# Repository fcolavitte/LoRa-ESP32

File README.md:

# LoRa-ESP32
Proyecto de comunicación unidireccional de USB a LoRa para pruebas de comunicación con satelites LEO para la empresa Satellogic.
El dispositivo toma datos por Wi-Fi y USB y envía mensajes por módulo LoRa E22 a satélites LEO.

El proyecto cuenta con una interfaz de usuario por USB con un menu interactivo por medio de los números del teclado.
La interfaz USB también admite comandos específicos.

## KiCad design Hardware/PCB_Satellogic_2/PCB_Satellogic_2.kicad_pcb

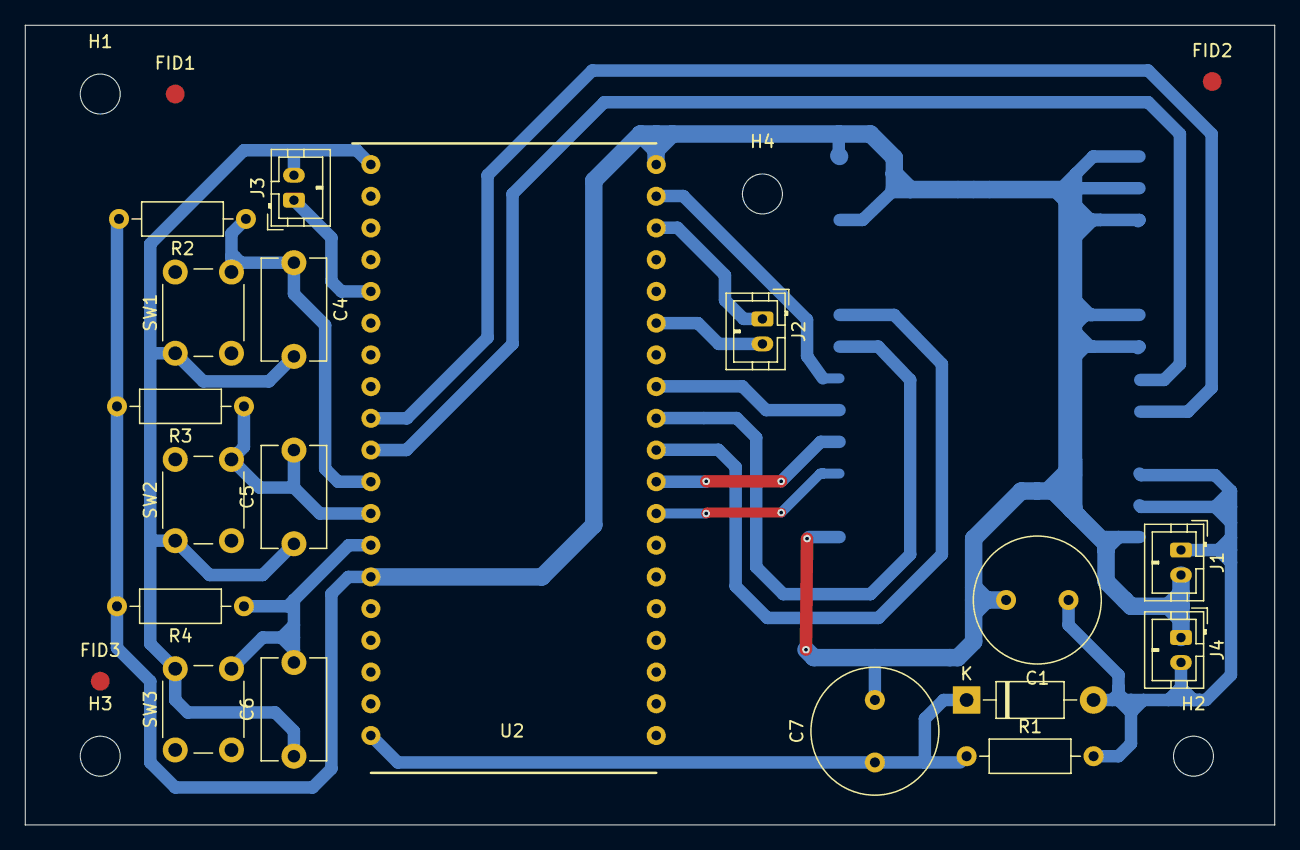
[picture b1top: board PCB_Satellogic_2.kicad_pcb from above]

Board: 2 copper layers, 100.0 x 64.0 mm, 26 parts (1 on the bottom side), 18 nets.

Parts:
C1: 470uF; C_Radial_D10.0mm_H16.0mm_P5.00mm
C4, C5, C6: 10nF; C_Disc_D8.0mm_W5.0mm_P7.50mm
C7: 4.7uF; C_Radial_D10.0mm_H16.0mm_P5.00mm
D1: 1N5819; D_DO-41_SOD81_P10.16mm_Horizontal
FID1, FID2, FID3: Fiducial; Fiducial_1.5mm_Mask3mm
H1, H2, H3, H4: MountingHole; MountingHole_3.2mm_M3
J1: 5V_out; JST_PH_B2B-PH-K_1x02_P2.00mm_Vertical
J2: I2C; JST_PH_B2B-PH-K_1x02_P2.00mm_Vertical
J3: ADC; JST_PH_B2B-PH-K_1x02_P2.00mm_Vertical
J4: 5V_in; JST_PH_B2B-PH-K_1x02_P2.00mm_Vertical
R1: 100R; R_Axial_DIN0207_L6.3mm_D2.5mm_P10.16mm_Horizontal
R2, R3, R4: 2k2; R_Axial_DIN0207_L6.3mm_D2.5mm_P10.16mm_Horizontal
SW1: SetRXMode; SW_PUSH_6mm_H4.3mm
SW2: TX; SW_PUSH_6mm_H4.3mm
SW3: SetWiFiMode; SW_PUSH_6mm_H4.3mm
U1: E22-900M30S_LoRa; E22-900M30S_LoRa_smd
U2: Node-MCU_ESP32_38PINES; Node-MCU_ESP32_38PINES_THT_offset

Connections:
/3v3: C4.2, C5.1, C6.1, J3.2, SW1.1, SW2.1, SW3.1, U2.1 (3.3V)
/5V: C1.1, D1.2 (A), J1.1, J4.2, R1.2, U1.9 (Vcc), U1.10 (Vcc)
/ADC: J3.1, U2.5 (GPIO34)
/BUSY: U1.14 (BUSY), U2.27 (Rx2-GPIO16)
/MISO: U1.16 (MISO), U2.31 (MISO-GPIO19)
/MOSI: U1.17 (MOSI), U2.37 (MOSI-GPIO23)
/NSS: U1.19 (NSS), U2.29 (CS0-GPIO5)
/RST_E22: U1.15 (NRST), U2.28 (Tx2-GPIO17)
/RXEN: U1.6 (RXEN), U2.10 (GPIO26)
/SCK: U1.18 (SCK), U2.30 (CLK-GPIO18)
/SCL: J2.1, U2.36 (GPIO22)
/SDA: J2.2, U2.33 (GPIO21)
/SetRxMode: C4.1, R2.1, SW1.2, U2.11 (GPIO27)
/SetWiFiMode: C6.2, R4.1, SW3.2, U2.13 (GPIO12)
/TX: C5.2, R3.1, SW2.2, U2.12 (GPIO14)
/TXEN: U1.7 (TXEN), U2.9 (GPIO25)
GND: C1.2, C7.2, J1.2, J4.1, R2.2, R3.2, R4.2, U1.1 (GND), U1.2 (GND), U1.3 (GND), U1.4 (GND), U1.5 (GND), U1.11 (GND), U1.12 (GND), U1.20 (GND), U1.22 (GND), U2.14 (GND), U2.38 (GND)
unnamed: C7.1, D1.1 (K), R1.1, U2.19 (Vin)

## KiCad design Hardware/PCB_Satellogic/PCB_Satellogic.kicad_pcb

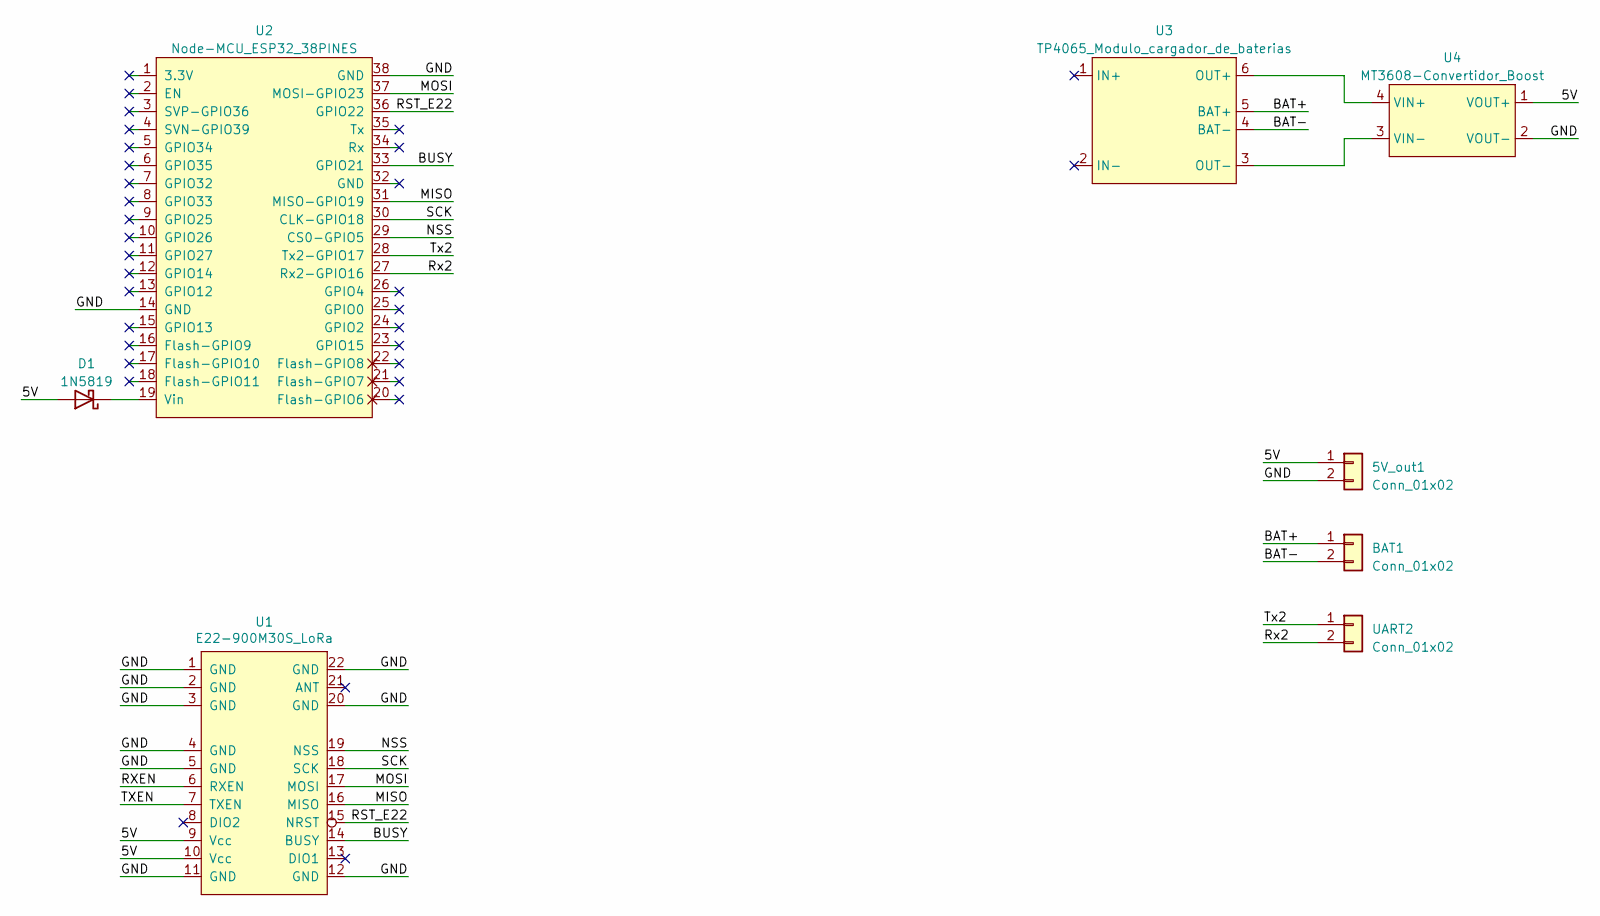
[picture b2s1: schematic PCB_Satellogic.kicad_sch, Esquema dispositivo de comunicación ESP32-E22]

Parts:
5V_out1: Conn_01x02; JST_PH_B2B-PH-K_1x02_P2.00mm_Vertical
BAT1: Conn_01x02; JST_PH_B2B-PH-K_1x02_P2.00mm_Vertical
D1: 1N5819; D_DO-41_SOD81_P10.16mm_Horizontal
U1: E22-900M30S_LoRa; E22-900M30S_LoRa_smd
U2: Node-MCU_ESP32_38PINES; Node-MCU_ESP32_38PINES_THT_offset
U3: TP4065_Modulo_cargador_de_baterias; TP4056 - Módulo de carga de batería
U4: MT3608-Convertidor_Boost
UART2: Conn_01x02; JST_PH_B2B-PH-K_1x02_P2.00mm_Vertical

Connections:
/5V: 5V_out1.1, D1.2 (A), U1.9 (Vcc), U1.10 (Vcc), U4.1 (VOUT+)
/BAT+: BAT1.1, U3.5 (BAT+)
/BAT-: BAT1.2, U3.4 (BAT-)
/BUSY: U1.14 (BUSY), U2.33 (GPIO21)
/GND: 5V_out1.2, U1.1 (GND), U1.2 (GND), U1.3 (GND), U1.4 (GND), U1.5 (GND), U1.11 (GND), U1.12 (GND), U1.20 (GND), U1.22 (GND), U2.14 (GND), U2.38 (GND), U4.2 (VOUT-)
/MISO: U1.16 (MISO), U2.31 (MISO-GPIO19)
/MOSI: U1.17 (MOSI), U2.37 (MOSI-GPIO23)
/NSS: U1.19 (NSS), U2.29 (CS0-GPIO5)
/RST_E22: U1.15 (NRST), U2.36 (GPIO22)
/RXEN: U1.6 (RXEN)
/Rx2: U2.27 (Rx2-GPIO16), UART2.2
/SCK: U1.18 (SCK), U2.30 (CLK-GPIO18)
/TXEN: U1.7 (TXEN)
/Tx2: U2.28 (Tx2-GPIO17), UART2.1
unnamed: D1.1 (K), U2.19 (Vin)
unnamed: U3.6 (OUT+), U4.4 (VIN+)
unnamed: U3.3 (OUT-), U4.3 (VIN-)

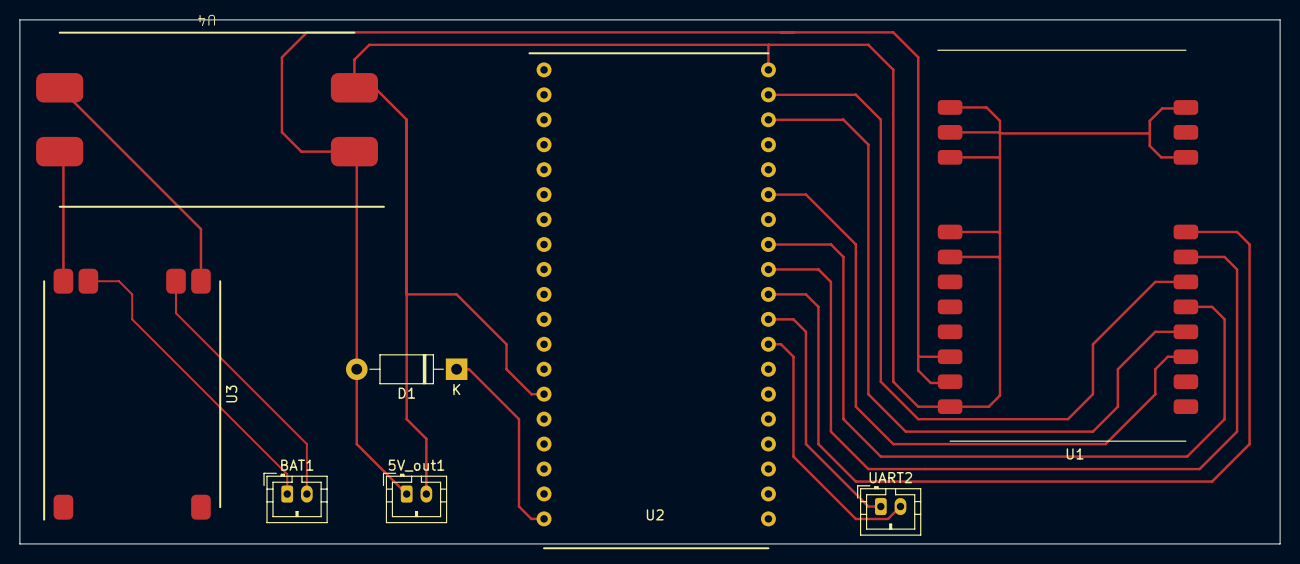
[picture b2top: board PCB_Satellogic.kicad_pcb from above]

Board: 2 copper layers, 128.3 x 53.3 mm, 8 parts (0 on the bottom side), 15 nets.

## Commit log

2023-03-07 Introducción HW
2023-05-20 Regularizacion del formato de archivos
2023-05-22 Se corrigieron includes
2023-05-22 Redacción de E22_port_ y comienzo de redacción del driver
2023-05-24 avances driver E22 y test de driver
2023-06-10 avances en RTC
2023-06-12 Modificación de API_time para usar RTC interno
2023-06-12 Correcciones menores en include de main.c
2023-06-12 Se verificó que el comando > escriba en ringbuffer y eliminó menú USB Firebase
2023-06-15 Se terminó API_time y se terminó de integrar con API_USB
2023-06-17 Corrección de bug al cargar fecha despues de las 21:00:00hs. Implementación del menu config_E22
2023-06-17 SE implementó MEF para envío de mensajes programados y beacon y se integró con interfaz USB
2023-06-17 Se integró la configuración vía Wi-Fi con la USB
2023-06-17 Se agregó posibilidad de modificar SSID y PASS a la que conectarse guardada en memoria no volatil. Se agregó reconexión automática a Wi-Fi.
2023-06-17 Se agregó comandos de reinicio y reconexión a Wi-Fi
2023-06-18 Se agregó función para poner al E22 en modo Rx para hacer la prueba entre dos dispositivos en tierra.
2023-06-27 pines TXEN y RXEN
2024-02-25 adición ; en saltos de línea antes de declaración de variables
2024-03-03 Se agregó SetModulationParams
2024-03-03 Se agregó palabra de sinc
2024-03-04 Se corrigieron detalles menores
2024-04-01 comparado con analizador logico
2024-04-02 actualizacion pasaje a vsc
2024-05-31 Se agregaron standbyte y DIO3, ya emite y visualiza el SDR
2024-06-03 Se agregó DIO3TCXO al RX
2024-06-08 se agregaron calibraciones
2024-06-09 Se hardcodeó transacciones SPI
2024-06-10 Se agregó función para ver registros
2024-06-14 Con esta modificacion ya se comunican los módulos
2024-06-14 Se emprolijó codigo de send y recibe mesage
2024-06-16 se corrijió largo de mensaje a enviar variable y se acomodaron comentarios de código
2024-06-17 Diseño PCB 2 con I2C para pantalla OLED y pulsadores
